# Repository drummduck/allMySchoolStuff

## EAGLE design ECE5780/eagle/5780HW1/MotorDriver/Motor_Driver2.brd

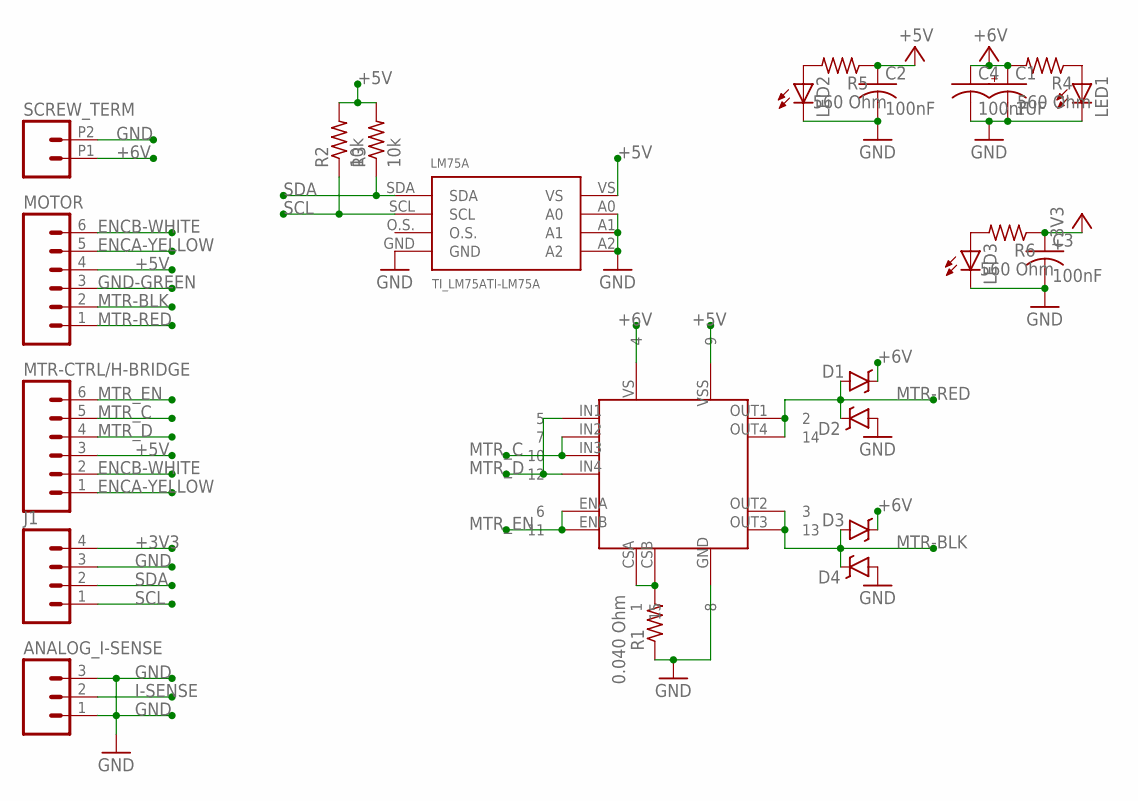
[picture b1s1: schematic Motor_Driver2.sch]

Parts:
ANALOG_I-SENSE: M03PTH; 1X03
C1: 1UF; CPOL-RADIAL-1UF-50V-KIT
C2, C3, C4: 100nF; C1206
D1, D2, D3, D4: B340A; SMA-DIODE
J1: M04PTH; 1X04
LED1, LED2, LED3: LEDSMT1206; 1206
LM75A: TI_LM75ATI-LM75A; TI_LM75A
MOTOR: M06SILK_FEMALE_PTH; 1X06
MTR-CTRL/H-BRIDGE: M06SILK_FEMALE_PTH; 1X06
R1: 0.040 Ohm; M0805
R2, R3: 10k; M1206
R4, R5, R6: 560 Ohm; M0805
SCREW_TERM: M022.54MM_SCREWTERM; 1X02_2.54_SCREWTERM
U$1: STL298N

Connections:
+3V3: C3.1, J1.4, R6.1
+5V: C2.1, LM75A.VS, MOTOR.4, MTR-CTRL/H-BRIDGE.3, R2.2, R3.2, R5.1
+6V: C1.1 (+), C4.1, D1.C, D3.C, R4.2, SCREW_TERM.P1 (1)
ENCA-YELLOW: MOTOR.5, MTR-CTRL/H-BRIDGE.1
ENCB-WHITE: MOTOR.6, MTR-CTRL/H-BRIDGE.2
GND: ANALOG_I-SENSE.1, ANALOG_I-SENSE.3, C1.2 (-), C2.2, C3.2, C4.2, D2.A, D4.A, J1.3, LED1.C, LED2.C, LED3.C, LM75A.A0, LM75A.A1, LM75A.A2, LM75A.GND, R1.1, SCREW_TERM.P2 (2)
GND-GREEN: MOTOR.3
I-SENSE: ANALOG_I-SENSE.2
MTR-BLK: D3.A, D4.C, MOTOR.2
MTR-RED: D1.A, D2.C, MOTOR.1
MTR_C: MTR-CTRL/H-BRIDGE.5
MTR_D: MTR-CTRL/H-BRIDGE.4
MTR_EN: MTR-CTRL/H-BRIDGE.6
unnamed: LED1.A, R4.1
unnamed: LED2.A, R5.2
unnamed: LED3.A, R6.2
SCL: J1.1, LM75A.SCL, R2.1
SDA: J1.2, LM75A.SDA, R3.1

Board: 2 copper layers, 24 parts (0 on the bottom side), 13 nets, no tracks yet.

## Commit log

2019-12-22 BoggleClientTest
2019-12-22 CS3710
2019-12-22 CS1410
2019-12-22 CS2420
2019-12-22 CS3505
2019-12-22 CS3991
2019-12-22 CS3992
2019-12-22 CS4150
2019-12-22 CS4400
2019-12-22 CS4530
2019-12-22 CS5530
2019-12-22 ECE2280
2019-12-22 ECE3030
2019-12-22 ECE5780
2019-12-22 ECECS3530
2019-12-22 CS3710Final
2021-01-21 Senior-Project: Tis good

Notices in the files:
parts and their libraries:
SparkFun-Connectors: Licensing: Creative Commons ShareAlike 4.0 International - https://creativecommons.org/licenses/by-sa/4.0
